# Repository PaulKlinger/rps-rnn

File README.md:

# RPS-RNN

The physical assembly of this project is pretty close to that of my [electronic dice](https://github.com/PaulKlinger/ndice). Some of the assembly tips there might also help here.

Components (mostly from aliexpress):
- 1 × [ATtiny1614 microcontroller](https://octopart.com/attiny1614-ssfr-microchip-82181131)
- [2mm PMMA optic fiber](https://www.aliexpress.com/item/5mX-Transparent-side-glow-plastic-PMMA-fiber-optic-cable-solid-core-optic-cable-diameter-2mm-3mm/32807597828.html)
- 1 × [10uf 0805 capacitor](https://www.aliexpress.com/item/100pcs-3-3PF-47UF-0805-SMD-100V-X7R-10-100nf-0-1uf-104K-104-22UF-4/32882102243.html)
- 3 × [10K 0805 resistor](https://www.aliexpress.com/item/100Pcs-0805-SMD-1-4W-0R-10M-chip-resistor-0-10R-100R-220R-330R-470R-1K/32858225842.html)
- 3 × [yellow 0805 LED](https://www.aliexpress.com/item/Free-Ship-100PCS-0805-light-emitting-diode-SMD-LED-bead-Red-Yellow-Green-White-Blue-Orange/32871959868.html)
- 1 × [coin cell battery holder](https://www.aliexpress.com/item/10PCS-Battery-Button-Cell-Holder-Socket-Case-CR2032-battery-holder-2032/32819924096.html)
- 3 × [smd switch](https://www.aliexpress.com/item/32752150129.html)
- 1 × [smd switch](https://www.aliexpress.com/item/32752118872.html)
- 1 × [smd slide switch](https://www.aliexpress.com/item/32967873133.html)

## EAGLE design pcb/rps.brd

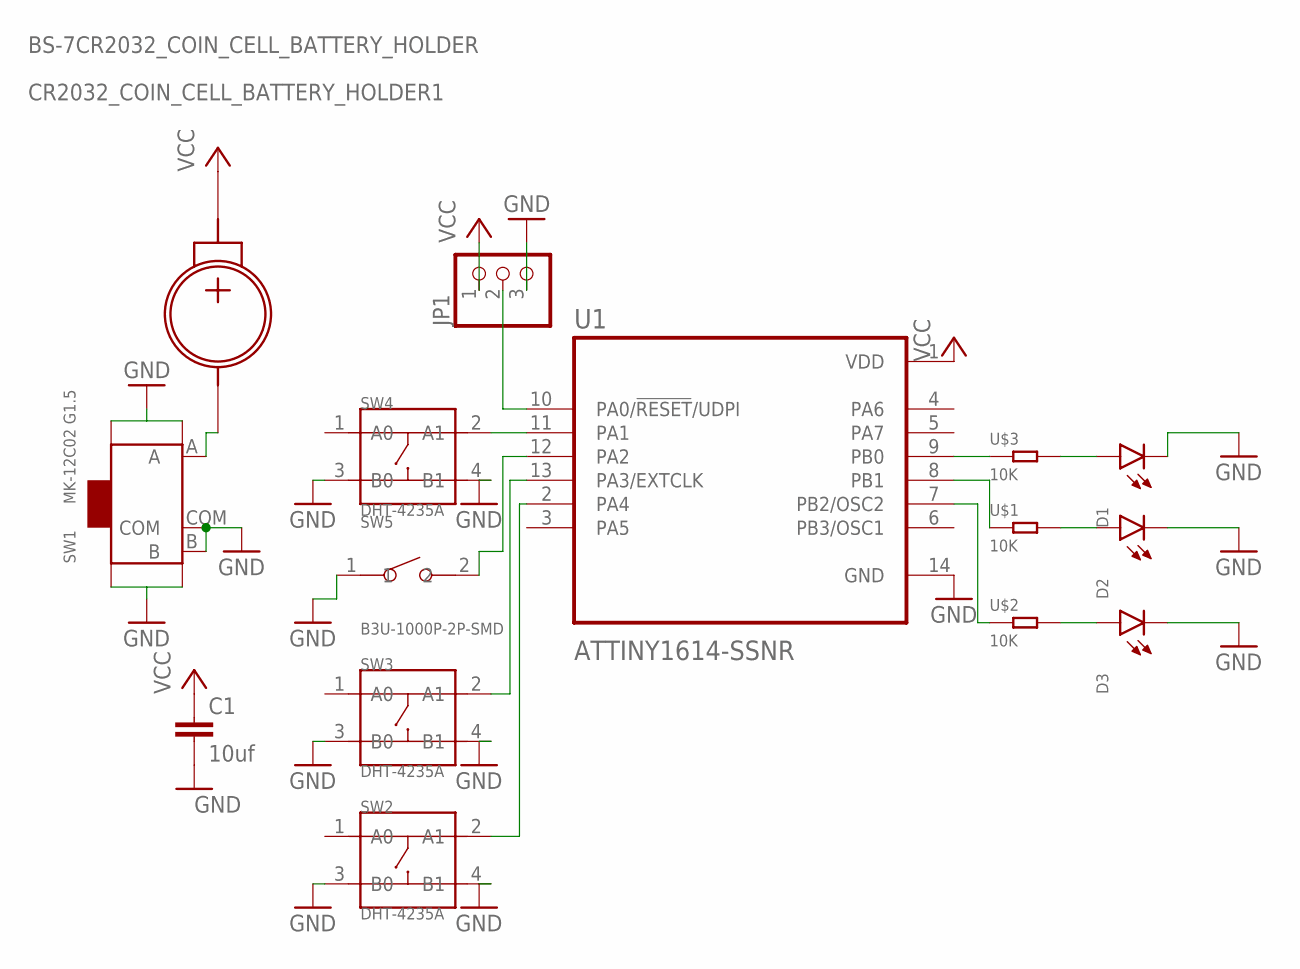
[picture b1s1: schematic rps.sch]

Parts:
C1: 10uf; C0805
CR2032_COIN_CELL_BATTERY_HOLDER1: BS-7CR2032_COIN_CELL_BATTERY_HOLDER; BS-7
D1, D2, D3: YELLOW-0805; SML0805
JP1: PINHD-1X3; 1X03
SW1: MK-12C02 G1.5; SW7-SMD-L6.7X2.7X3.2MM
SW2, SW3, SW4: DHT-4235A; SW4-SMD-4.2X3.2X2.5MM
SW5: B3U-1000P-2P-SMD; SW2-2.6-3.0X2.5X1.2+0.4MM
U1: ATTINY1614-SSNR; SOIC127P600X175-14N
U$1, U$2, U$3: 10K; R0805

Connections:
GND: C1.2, D1.C, D2.C, D3.C, JP1.3, SW1.B, SW1.COM, SW1.SS1, SW1.SS2, SW1.SS3, SW1.SS4, SW2.3 (B0), SW2.4 (B1), SW3.3 (B0), SW3.4 (B1), SW4.3 (B0), SW4.4 (B1), SW5.1, U1.14 (GND)
unnamed: JP1.2, U1.10 (PA0/!RESET!/UDPI)
unnamed: SW4.2 (A1), U1.11 (PA1)
unnamed: SW5.2, U1.12 (PA2)
unnamed: SW3.2 (A1), U1.13 (PA3/EXTCLK)
unnamed: SW2.2 (A1), U1.2 (PA4)
unnamed: U1.9 (PB0), U$3.1
unnamed: U1.8 (PB1), U$1.1
unnamed: U1.7 (PB2/OSC2), U$2.1
unnamed: D1.A, U$3.2
unnamed: D2.A, U$1.2
unnamed: D3.A, U$2.2
NEG: CR2032_COIN_CELL_BATTERY_HOLDER1.NEG, SW1.A
VCC: C1.1, CR2032_COIN_CELL_BATTERY_HOLDER1.POS, JP1.1, U1.1 (VDD)

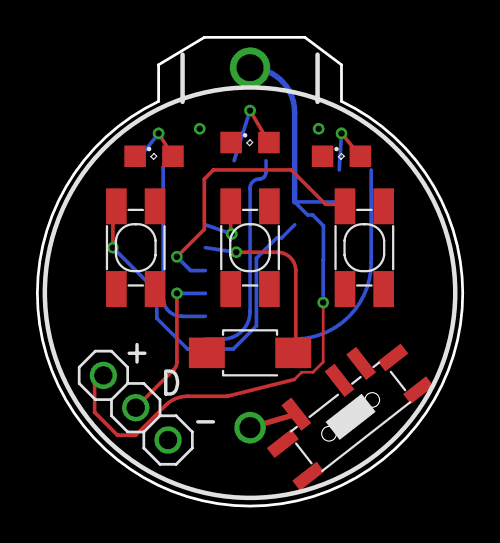
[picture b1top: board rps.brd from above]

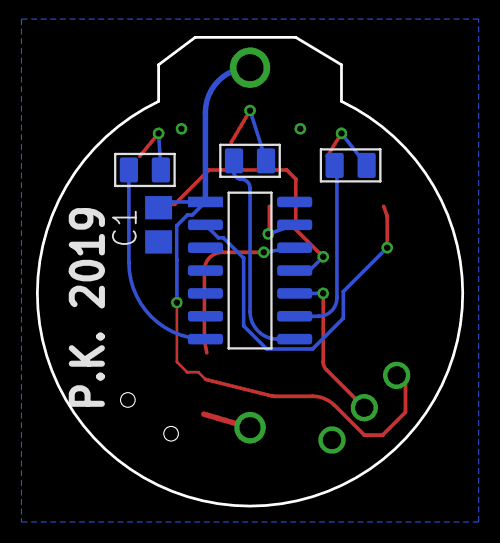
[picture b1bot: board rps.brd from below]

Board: 2 copper layers, 23.6 x 26.0 mm, 15 parts (5 on the bottom side), 14 nets.

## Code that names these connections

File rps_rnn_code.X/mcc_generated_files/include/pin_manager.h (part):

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/**
 * \brief Set IO_PA2 input/sense configuration
 *
 * Enable/disable IO_PA2 digital input buffer and pin change interrupt,
 * select pin interrupt edge/level sensing mode
 *
 * \param[in] isc PORT_ISC_INTDISABLE_gc    = Interrupt disabled but input buffer enabled
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/**
 * \brief Set IO_PB2 input/sense configuration
 *
 * Enable/disable IO_PB2 digital input buffer and pin change interrupt,
 * select pin interrupt edge/level sensing mode
 *
 * \param[in] isc PORT_ISC_INTDISABLE_gc    = Interrupt disabled but input buffer enabled
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/**
 * \brief Set IO_PA1 input/sense configuration
 *
 * Enable/disable IO_PA1 digital input buffer and pin change interrupt,
 * select pin interrupt edge/level sensing mode
 *
 * \param[in] isc PORT_ISC_INTDISABLE_gc    = Interrupt disabled but input buffer enabled
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/**
 * \brief Set IO_PA4 input/sense configuration
 *
 * Enable/disable IO_PA4 digital input buffer and pin change interrupt,
 * select pin interrupt edge/level sensing mode
 *
 * \param[in] isc PORT_ISC_INTDISABLE_gc    = Interrupt disabled but input buffer enabled
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/**
 * \brief Set IO_PA3 input/sense configuration
 *
 * Enable/disable IO_PA3 digital input buffer and pin change interrupt,
 * select pin interrupt edge/level sensing mode
 *
 * \param[in] isc PORT_ISC_INTDISABLE_gc    = Interrupt disabled but input buffer enabled
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/**
 * \brief Set IO_PB1 input/sense configuration
 *
 * Enable/disable IO_PB1 digital input buffer and pin change interrupt,
 * select pin interrupt edge/level sensing mode
 *
 * \param[in] isc PORT_ISC_INTDISABLE_gc    = Interrupt disabled but input buffer enabled
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/**
 * \brief Set IO_PB0 input/sense configuration
 *
 * Enable/disable IO_PB0 digital input buffer and pin change interrupt,
 * select pin interrupt edge/level sensing mode
 *
 * \param[in] isc PORT_ISC_INTDISABLE_gc    = Interrupt disabled but input buffer enabled
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
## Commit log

2019-06-27 added pcbs
2019-06-27 initial commit of code, currently just experiments
2019-06-27 Added weights, started work on model functions
2019-07-03 progress on simple model evaluation
2019-07-03 return our next move instead of opponents predicted one
2019-07-03 fixed a bunch of stupid errors in simple model calculation
    first move gives correct result now, with some inaccuracies due to tanh (will replace with softsign)
    still need to test later moves and sampling
2019-07-03 seed random number generator, bugfix
    sampling seems to work
2019-07-03 corrected temperature (was inverted), prevent overflow in softmax
2019-07-03 made names for matrix functions more uniform and added comments
2019-07-04 performance optimisation for m_mult_fq
2019-07-04 corrected comment
2019-07-04 made weights const, added m_softsign_f function
    const variables are stored in progmem instead of ram
2019-07-04 moved recurrent layer calculation to function, in preparation for multi-layer model
2019-07-05 changed to 3 layer model, corrected set_input (opponents move comes first)
2019-07-05 set up pins correctly, added code in main.c for assembly testing
2019-07-05 removed debugging variables
2019-07-06 working main loop, seeding of RNG from timer
2019-07-06 adjusted pad sizes for buttons on PCB
2019-07-06 Added 3d printed parts and Fusion 360 model
2019-07-06 added 2nd mode (use rps-rnn to play against another person)
2019-07-06 renamed simple_model to model
2019-07-06 Added notebooks for network training/testing and data
2019-07-06 added comment noting which version of the weights is used
2019-07-06 added missing project files
2019-07-06 added binaries
2019-07-06 added gerbers
2019-07-06 added RNN architecture diagram
2019-07-07 added/corrected diagrams
2019-07-07 tweaked diagrams
2019-07-07 added readme
2019-07-07 Create LICENSE
2019-07-07 tweaked readme
2019-07-07 use expected score to select which move to play
    Instead of just playing the move that does best
    against the predicted one, use all the information available
    in the predicted probabilities to select the one that
    optimizes the expected score. E.g. when the predicted
    probabilities for opponent move are (0.1,0.44,0.46) play
    scissors instead of rock.
2019-07-07 changed temperature back from testing value
2019-07-07 updated binary
2019-07-08 minor changes to top cover model
2019-07-19 corrected link

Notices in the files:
rps_rnn_code.X/mcc_generated_files/include/pin_manager.h:
(c) 2018 Microchip Technology Inc. and its subsidiaries.
